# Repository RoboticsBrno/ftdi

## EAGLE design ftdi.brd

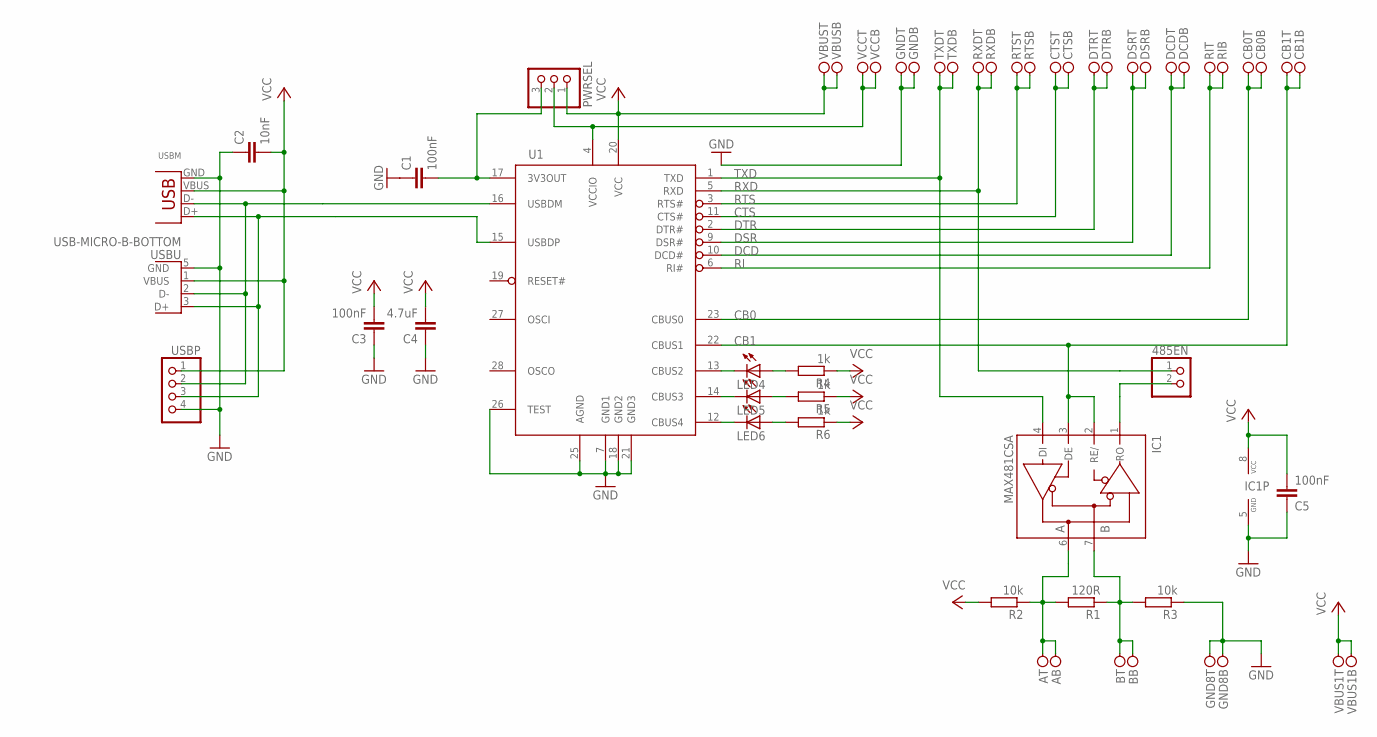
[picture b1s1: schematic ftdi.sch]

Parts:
485EN: PINHD-1X2/90; 1X02/90
A: PINH2X01; PINH2X01SMD
B: PINH2X01; PINH2X01SMD
C1, C3, C5: 100nF; C0402
C2: 10nF; C0603
C4: 4.7uF; C0805K
CB0, CB1: PINH2X01; PINH2X01SMD
CTS: PINH2X01; PINH2X01SMD
DCD: PINH2X01; PINH2X01SMD
DSR: PINH2X01; PINH2X01SMD
DTR: PINH2X01; PINH2X01SMD
GND, GND8: PINH2X01; PINH2X01SMD
IC1: MAX481CSA; SO08
LED4, LED5, LED6: LEDCHIPLED_0603; CHIPLED_0603
PWRSEL: PINHD-1X3/90; 1X03/90
R1: 120R; R0603
R2, R3: 10k; R0603
R4, R5, R6: 1k; R0603
RI: PINH2X01; PINH2X01SMD
RTS: PINH2X01; PINH2X01SMD
RXD: PINH2X01; PINH2X01SMD
TXD: PINH2X01; PINH2X01SMD
U1: FT232RL; SSOP28DB
USBM: USB-MB-S
USBP: PINHD-1X4; 1X04
USBU: USB-MICRO-B-BOTTOM; USB-MICRO-B-BOTTOM-MOLEX
VBUS, VBUS1: PINH2X01; PINH2X01SMD
VCC: PINH2X01; PINH2X01SMD

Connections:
3V3: C1.2, PWRSEL.3, U1.17 (3V3OUT)
A: A.1, A.2, IC1.6 (A), R1.2, R2.1
B: B.1, B.2, IC1.7 (B), R1.1, R3.2
CB0: CB0.1, CB0.2, U1.23 (CBUS0)
CB1: CB1.1, CB1.2, IC1.2 (RE/), IC1.3 (DE), U1.22 (CBUS1)
CB2_: LED4.A, R4.2
CB3_: LED5.A, R5.2
CB4_: LED6.A, R6.2
CBUS2_: LED4.C, U1.13 (CBUS2)
CBUS3_: LED5.C, U1.14 (CBUS3)
CBUS4_: LED6.C, U1.12 (CBUS4)
CTS: CTS.1, CTS.2, U1.11 (CTS#)
DCD: DCD.1, DCD.2, U1.10 (DCD#)
DSR: DSR.1, DSR.2, U1.9 (DSR#)
DTR: DTR.1, DTR.2, U1.2 (DTR#)
GND: C1.1, C2.1, C3.1, C4.1, C5.1, GND.1, GND.2, GND8.1, GND8.2, IC1.5 (GND), R3.1, U1.7 (GND1), U1.18 (GND2), U1.21 (GND3), U1.25 (AGND), U1.26 (TEST), USBM.GND, USBP.4, USBU.5 (GND)
RI: RI.1, RI.2, U1.6 (RI#)
RO: 485EN.2, IC1.1 (RO)
RTS: RTS.1, RTS.2, U1.3 (RTS#)
RXD: 485EN.1, RXD.1, RXD.2, U1.5 (RXD)
TXD: IC1.4 (DI), TXD.1, TXD.2, U1.1 (TXD)
USBDM: U1.16 (USBDM), USBM.D-, USBP.2, USBU.2 (D-)
USBDP: U1.15 (USBDP), USBM.D+, USBP.3, USBU.3 (D+)
VCC: C2.2, C3.2, C4.2, C5.2, IC1.8 (VCC), PWRSEL.1, R2.2, R4.1, R5.1, R6.1, U1.20 (VCC), USBM.VBUS, USBP.1, USBU.1 (VBUS), VBUS.1, VBUS.2, VBUS1.1, VBUS1.2
VCCIO: PWRSEL.2, U1.4 (VCCIO), VCC.1, VCC.2

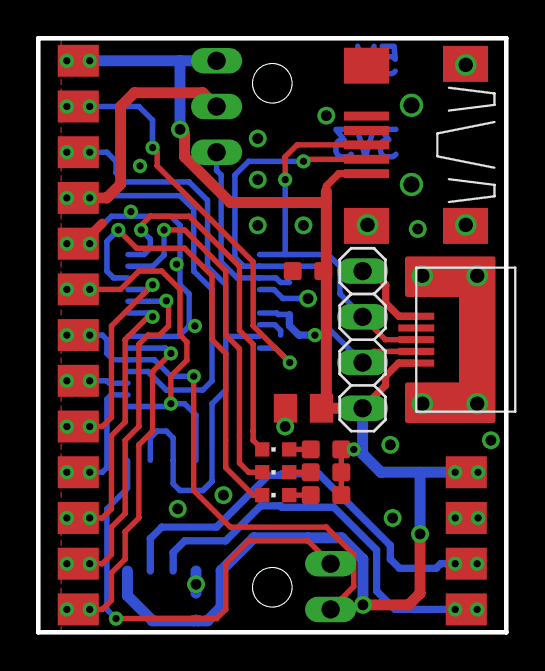
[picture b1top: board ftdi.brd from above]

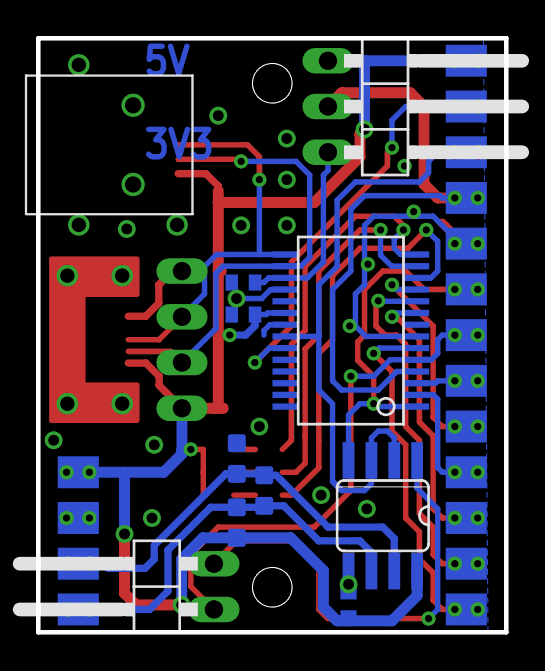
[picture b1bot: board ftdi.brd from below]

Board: 2 copper layers, 26.0 x 33.0 mm, 38 parts (10 on the bottom side), 25 nets.

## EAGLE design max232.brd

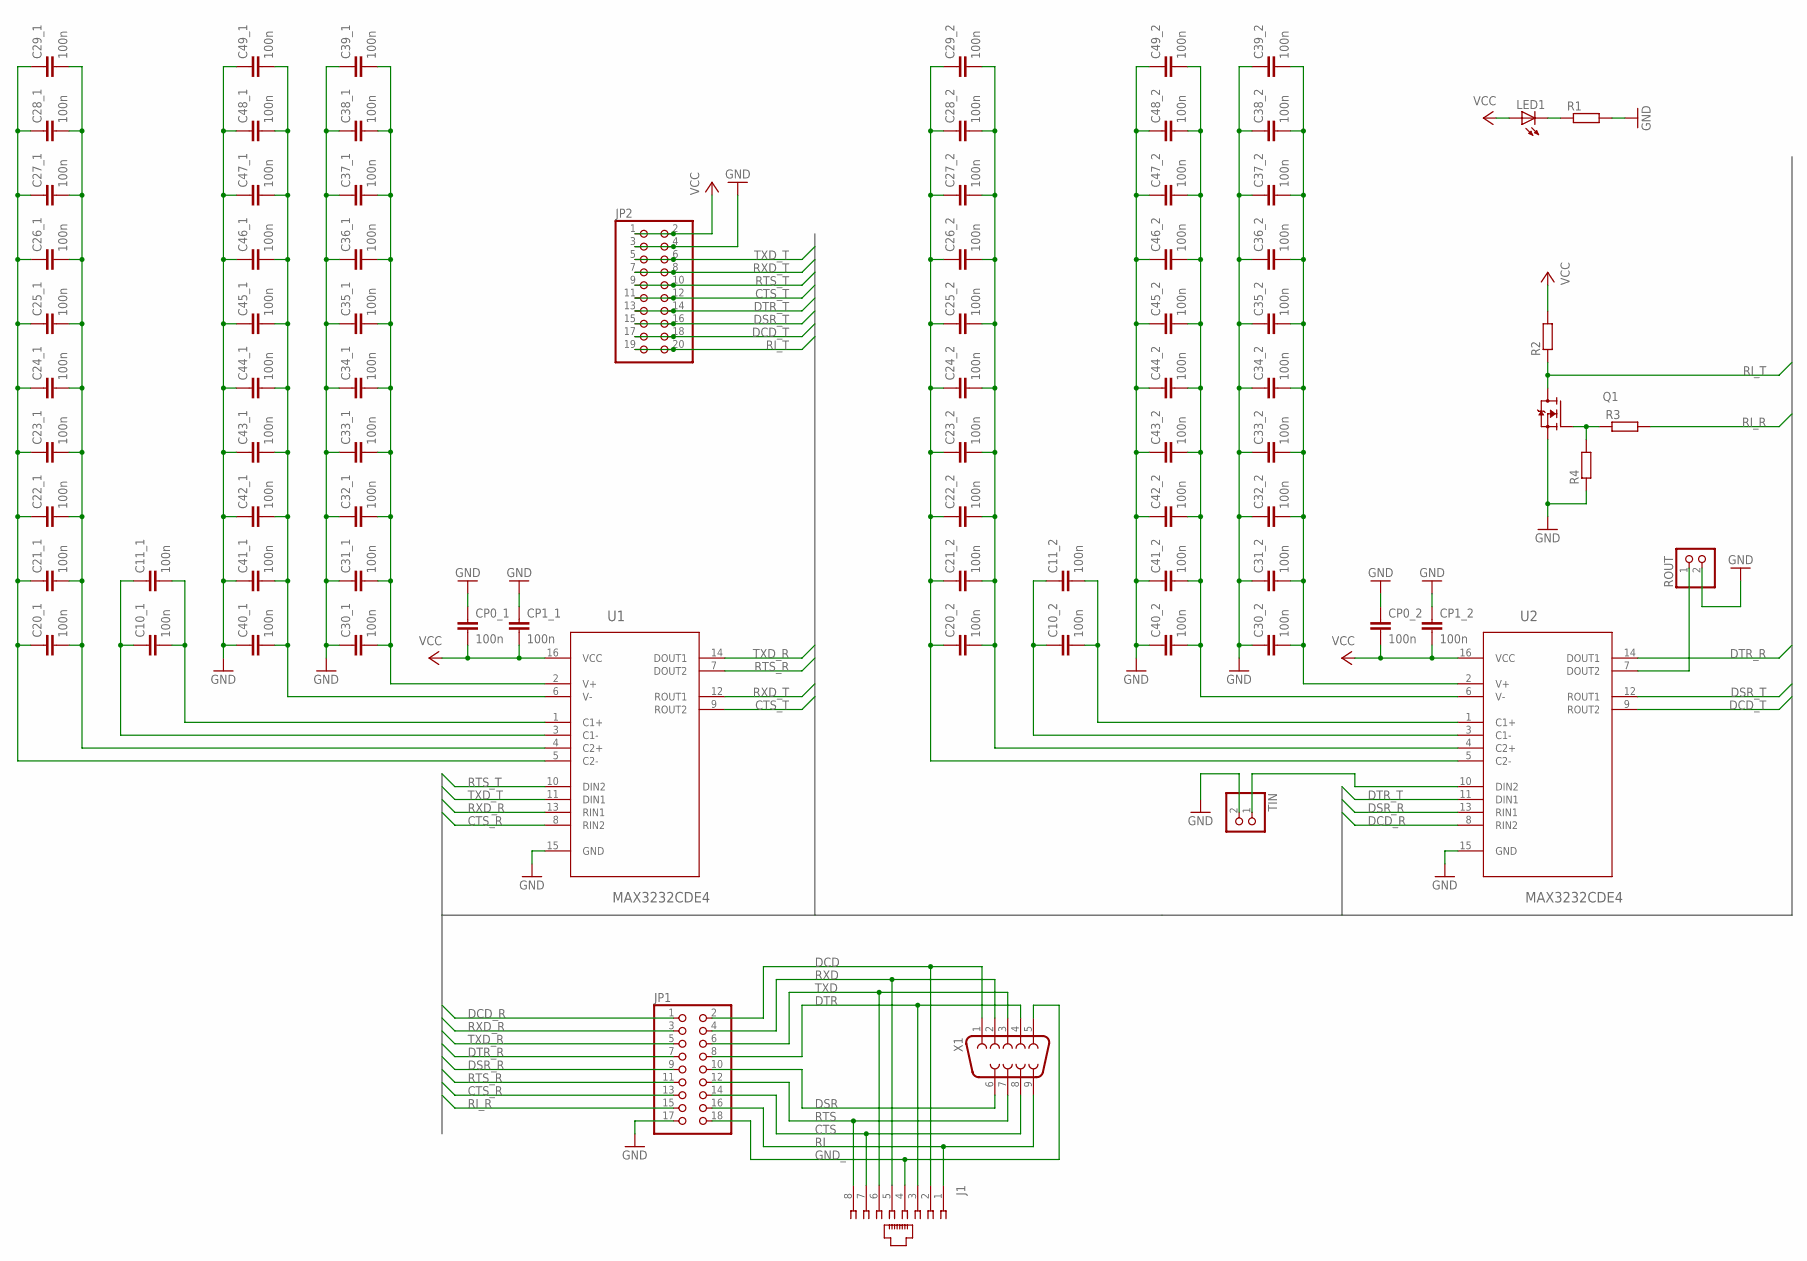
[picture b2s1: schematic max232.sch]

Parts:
C10_1, C10_2, C11_1, C11_2, C20_1, C20_2, C21_1, C21_2, C22_1, C22_2, C23_1, C23_2, C24_1, C24_2, C25_1, C25_2, C26_1, C26_2, C27_1, C27_2, C28_1, C28_2, C29_1, C29_2, C30_1, C30_2, C31_1, C31_2, C32_1, C32_2, C33_1, C33_2, C34_1, C34_2, C35_1, C35_2, C36_1, C36_2, C37_1, C37_2, C38_1, C38_2, C39_1, C39_2, C40_1, C40_2, C41_1, C41_2, C42_1, C42_2, C43_1, C43_2, C44_1, C44_2, C45_1, C45_2, C46_1, C46_2, C47_1, C47_2, C48_1, C48_2, C49_1, C49_2: 100n; C0402
CP0_1, CP0_2, CP1_1, CP1_2: 100n; C0402
J1: 215877-4
JP1: PINHD-2X9; 2X09
JP2: PINHD-2X10/90; 2X10/90
LED1: LEDCHIP-LED0603; CHIP-LED0603
Q1: N-MOSFET-SOT23-GSD; SOT23
R1, R2, R3, R4: R-EU_R0603; R0603
ROUT: PINHD-1X2; 1X02
TIN: PINHD-1X2; 1X02
U1, U2: MAX3232CDE4; SOIC127P600X175-16N
X1: F09HP

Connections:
C1+1: C10_1.2, C11_1.2, U1.1 (C1+)
C1+2: C10_2.2, C11_2.2, U2.1 (C1+)
C1-1: C10_1.1, C11_1.1, U1.3 (C1-)
C1-2: C10_2.1, C11_2.1, U2.3 (C1-)
C2+1: C20_1.2, C21_1.2, C22_1.2, C23_1.2, C24_1.2, C25_1.2, C26_1.2, C27_1.2, C28_1.2, C29_1.2, U1.4 (C2+)
C2+2: C20_2.2, C21_2.2, C22_2.2, C23_2.2, C24_2.2, C25_2.2, C26_2.2, C27_2.2, C28_2.2, C29_2.2, U2.4 (C2+)
C2-1: C20_1.1, C21_1.1, C22_1.1, C23_1.1, C24_1.1, C25_1.1, C26_1.1, C27_1.1, C28_1.1, C29_1.1, U1.5 (C2-)
C2-2: C20_2.1, C21_2.1, C22_2.1, C23_2.1, C24_2.1, C25_2.1, C26_2.1, C27_2.1, C28_2.1, C29_2.1, U2.5 (C2-)
CTS: J1.7, JP1.14, X1.8
CTS_R: JP1.13, U1.8 (RIN2)
CTS_T: JP2.11, JP2.12, U1.9 (ROUT2)
DCD: J1.2, JP1.2, X1.1
DCD_R: JP1.1, U2.8 (RIN2)
DCD_T: JP2.17, JP2.18, U2.9 (ROUT2)
DSR: JP1.10, X1.6
DSR_R: JP1.9, U2.13 (RIN1)
DSR_T: JP2.15, JP2.16, U2.12 (ROUT1)
DTR: J1.3, JP1.8, X1.4
DTR_R: JP1.7, U2.14 (DOUT1)
DTR_T: JP2.13, JP2.14, U2.11 (DIN1)
GND: C30_1.1, C30_2.1, C31_1.1, C31_2.1, C32_1.1, C32_2.1, C33_1.1, C33_2.1, C34_1.1, C34_2.1, C35_1.1, C35_2.1, C36_1.1, C36_2.1, C37_1.1, C37_2.1, C38_1.1, C38_2.1, C39_1.1, C39_2.1, C40_1.1, C40_2.1, C41_1.1, C41_2.1, C42_1.1, C42_2.1, C43_1.1, C43_2.1, C44_1.1, C44_2.1, C45_1.1, C45_2.1, C46_1.1, C46_2.1, C47_1.1, C47_2.1, C48_1.1, C48_2.1, C49_1.1, C49_2.1, CP0_1.1, CP0_2.1, CP1_1.1, CP1_2.1, JP1.17, JP2.3, JP2.4, Q1.2 (S), R1.2, R4.1, ROUT.2, TIN.2, U1.15 (GND), U2.15 (GND)
GND_: J1.4, JP1.18, X1.5
PWR_LED: LED1.C, R1.1
RI: J1.1, JP1.16, X1.9
RI_G: Q1.1 (G), R3.1, R4.2
RI_R: JP1.15, R3.2
RI_T: JP2.19, JP2.20, Q1.3 (D), R2.1
ROUT: ROUT.1, U2.7 (DOUT2)
RTS: J1.8, JP1.12, X1.7
RTS_R: JP1.11, U1.7 (DOUT2)
RTS_T: JP2.9, JP2.10, U1.10 (DIN2)
RXD: J1.5, JP1.4, X1.2
RXD_R: JP1.3, U1.13 (RIN1)
RXD_T: JP2.7, JP2.8, U1.12 (ROUT1)
TIN: TIN.1, U2.10 (DIN2)
TXD: J1.6, JP1.6, X1.3
TXD_R: JP1.5, U1.14 (DOUT1)
TXD_T: JP2.5, JP2.6, U1.11 (DIN1)
V+1: C30_1.2, C31_1.2, C32_1.2, C33_1.2, C34_1.2, C35_1.2, C36_1.2, C37_1.2, C38_1.2, C39_1.2, U1.2 (V+)
V+2: C30_2.2, C31_2.2, C32_2.2, C33_2.2, C34_2.2, C35_2.2, C36_2.2, C37_2.2, C38_2.2, C39_2.2, U2.2 (V+)
V-1: C40_1.2, C41_1.2, C42_1.2, C43_1.2, C44_1.2, C45_1.2, C46_1.2, C47_1.2, C48_1.2, C49_1.2, U1.6 (V-)
V-2: C40_2.2, C41_2.2, C42_2.2, C43_2.2, C44_2.2, C45_2.2, C46_2.2, C47_2.2, C48_2.2, C49_2.2, U2.6 (V-)
VCC: CP0_1.2, CP0_2.2, CP1_1.2, CP1_2.2, JP2.1, JP2.2, LED1.A, R2.2, U1.16 (VCC), U2.16 (VCC)

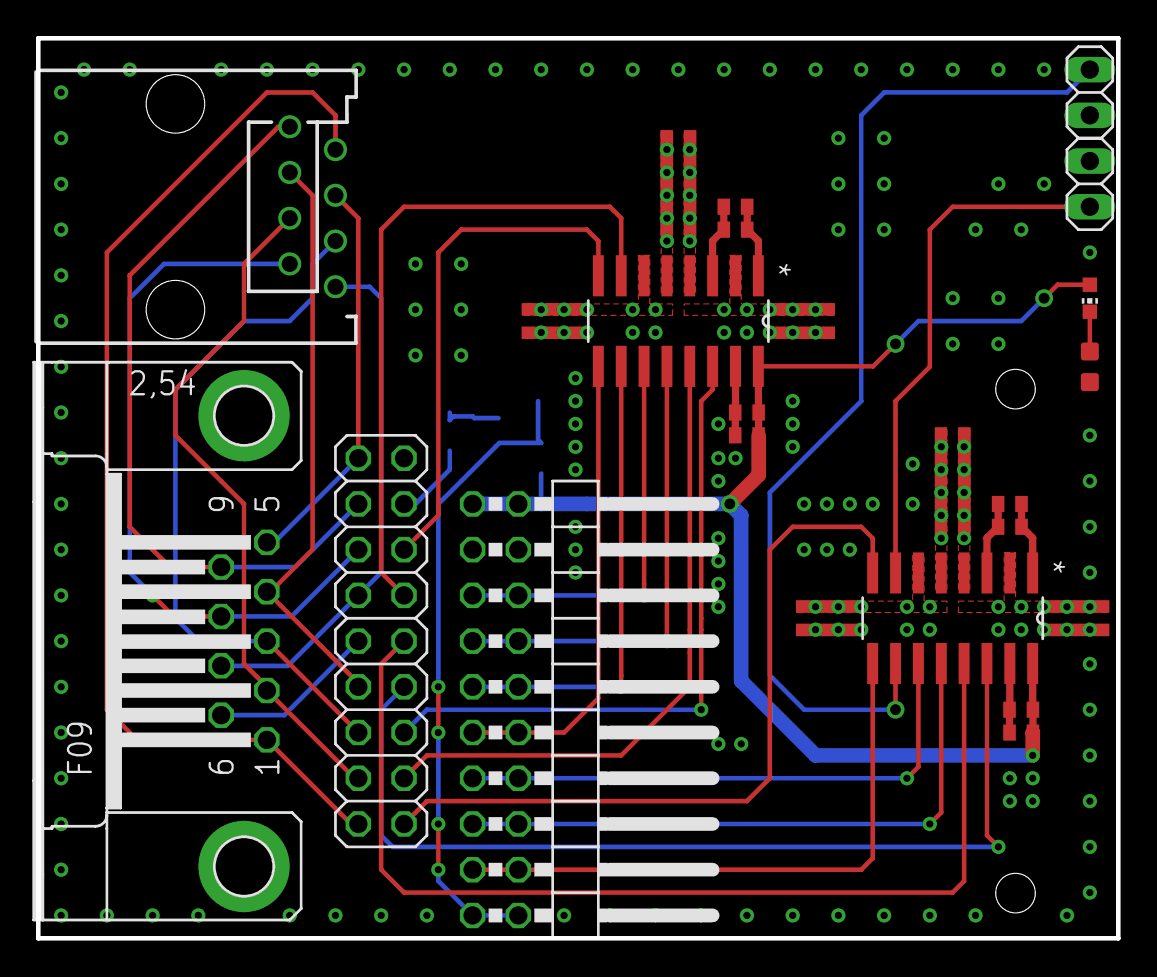
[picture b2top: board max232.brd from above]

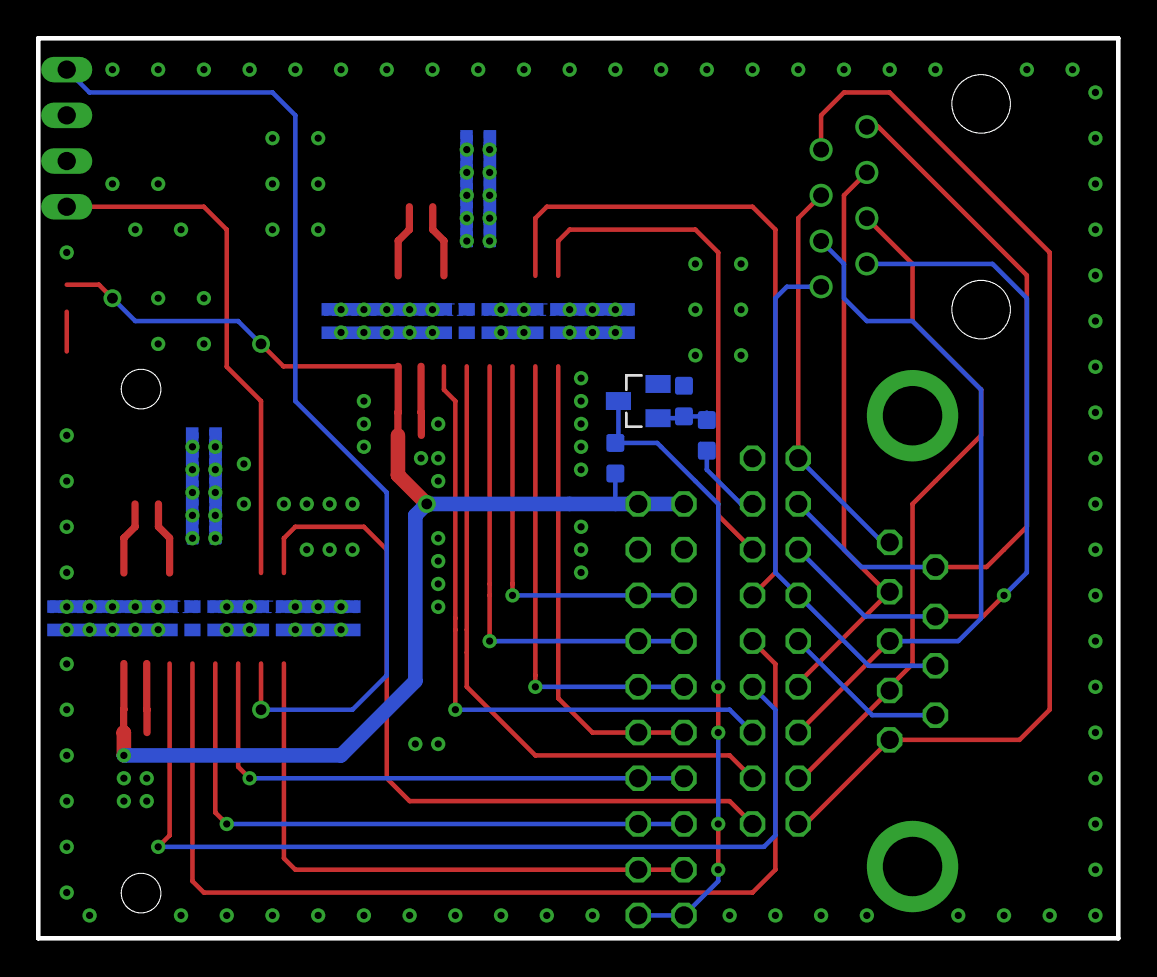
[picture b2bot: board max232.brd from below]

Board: 2 copper layers, 60.0 x 50.0 mm, 82 parts (42 on the bottom side), 43 nets.

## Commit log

2011-01-16 IO connector: RX, TX, GND, VCC (bus power); selectable IO voltage (internaly 5V/3.3V, optyonaly external voltage); 3 programable LEDs
2011-01-16 IO connector: CBUS1, CBUS0 (programmable IOs); RX; TX; GND; VCC (bus power)+ CTS, RI, RTS. selectable IO voltage (internaly 5V/3.3V, optyonaly external voltage); 3 programable LEDs
2011-01-17 Changed the pin layout to a compatible one. Rerouted.
2012-01-13 Edit schema and board. Rerouted.
2012-03-26 Edit board. Version 4. Use for production.
2014-09-21 draft v5 - mini USB / micto USB / pinhead - all serial port signals - selectable max485 - mounting holes
2014-09-22 small changes in ground plane and USB connectors mounting
2014-10-22 added hgignore
2014-11-11 added RS232 adapter
2014-11-11 fixed DRC in max232
2014-11-11 updated libraries and fixed DRC
2014-12-03 Added tag ftdi v5; max232 v1.0 for changeset 1cf76a46de00
